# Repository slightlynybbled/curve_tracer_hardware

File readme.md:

# Purpose #

The purpose of this repository is to document the curve tracer project.  A
full description may be found at [for(embed)](http://www.forembed.com/project-curve-tracer-requirements.html).

# Project Repositories #

Be sure to check out the [firmware](https://github.com/slightlynybbled/curve_tracer_firmware) and 
[gui](https://github.com/slightlynybbled/curve_tracer_gui) repositories!

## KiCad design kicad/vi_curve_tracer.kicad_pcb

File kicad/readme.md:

# Electronics #

This directory contains the schematics and PCB layout (KiCad)

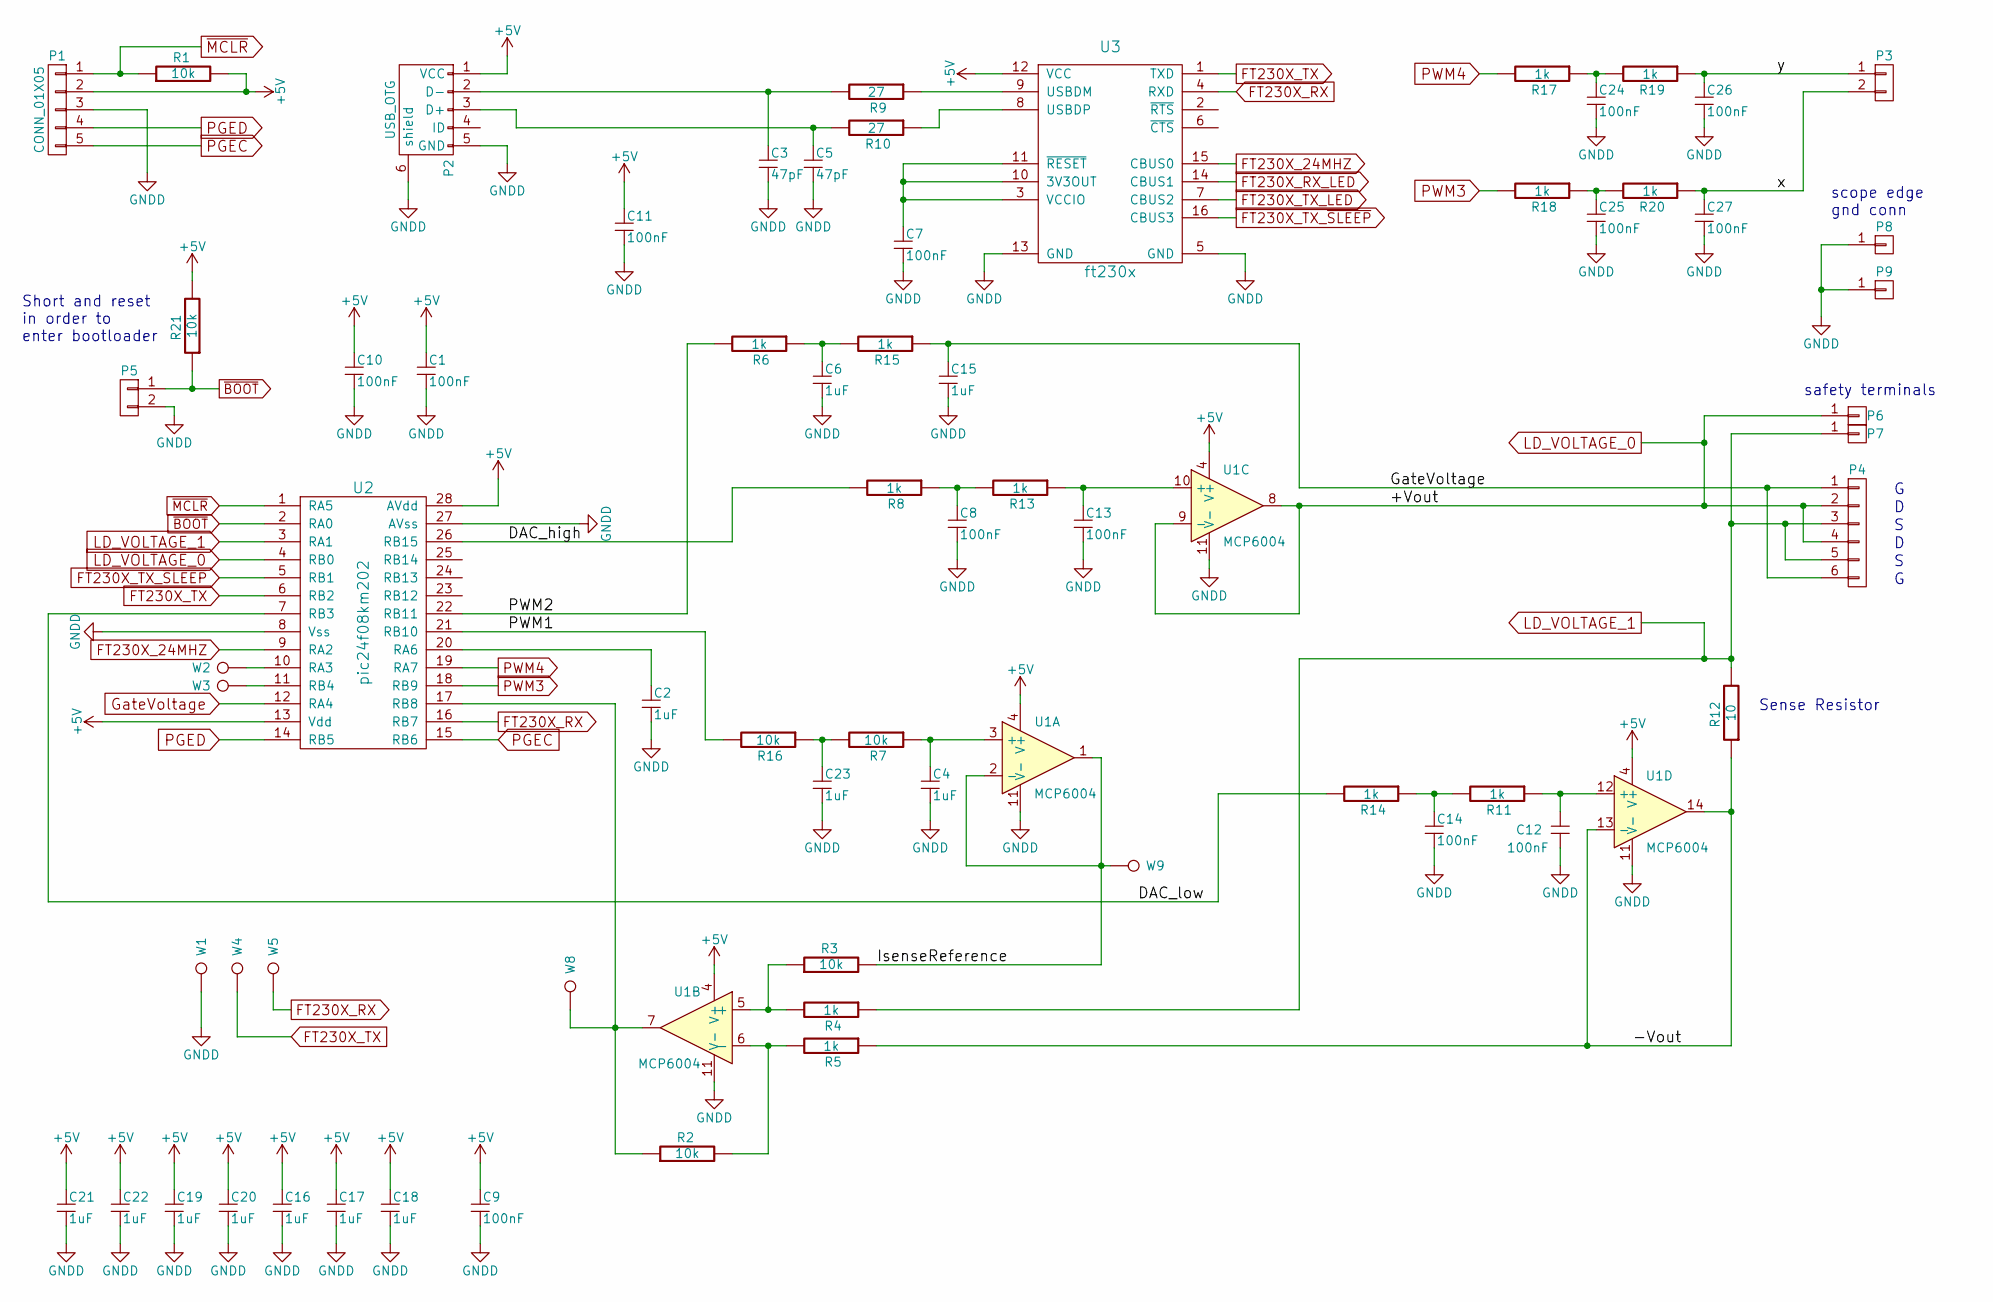
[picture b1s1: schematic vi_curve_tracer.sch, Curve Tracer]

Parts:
C1, C7, C8, C9, C10, C11, C12, C13, C14, C24, C25, C26, C27: 100nF; SM_0603; MPN CC0603ZRY5V7BB104
C2, C4, C6, C15, C16, C17, C18, C19, C20, C21, C22, C23: 1uF; SM_0603; MPN CC0603ZRY5V7BB105
C3, C5: 47pF; SM_0603; MPN C0603C470J3GACTU
P1: CONN_01X05; CONN_1x5_0.1in
P2: USB_OTG; CONN_USB; MPN DX4R005JJ2R1800
P3: CONN_01X02; CON_1x2_0.1in; MPN 0022284020
P4: CONN_01X06; CONN_2x3_SOCKET; MPN A06-LC-TT
P5: CONN_01X02; Pin_Header_Straight_1x02
P6: CONN_01X01; CONN_1x1_CT3150; MPN CT3150-2
P7: CONN_01X01; CONN_1x1_CT3150; MPN CT3150-0
P8, P9: CONN_01X01; CONN_1x1_EDGE_SCOPE_GND
R1, R2, R3, R7, R16, R21: 10k; SM_0603; MPN RC0603FR-0710KL
R4, R5, R6, R8, R11, R13, R14, R15, R17, R18, R19, R20: 1k; SM_0603; MPN RC0603FR-071KL
R9, R10: 27; SM_0603; MPN RC0603FR-0727RL
R12: 10; SM_0603; MPN RC0603FR-0710RL
U1: MCP6004; SSOP-14; MPN MCP6L04T-E/ST
U2: pic24f08km202; SSOP-28; MPN PIC24FV16KM202-I/SS
U3: ft230x; SOIC-16; MPN FT230XS-R
W1, W2, W3, W4, W5, W8, W9: TEST_1P; Measurement_Point_Round-SMD-Pad_Small

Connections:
+5V: C1.1, C9.1, C10.1, C11.1, C16.1, C17.1, C18.1, C19.1, C20.1, C21.1, C22.1, P1.2, P2.1 (VCC), R1.2, R21.2, U1.4 (V+), U2.13 (Vdd), U2.28 (AVdd), U3.12 (VCC)
/-Vout: R5.1, R12.1, U1.13 (-), U1.14
/DAC_high: R8.2, U2.26 (RB15)
/DAC_low: R14.2, U2.7 (RB3)
/IsenseReference: R3.2, U1.1, U1.2 (-), W9.1
/PWM1: R16.2, U2.21 (RB10)
/PWM2: R6.2, U2.22 (RB11)
/x: C27.1, P3.2, R20.1
/y: C26.1, P3.1, R19.1
FT230X_24MHZ: U2.9 (RA2), U3.15 (CBUS0)
FT230X_RX: U2.16 (RB7), U3.4 (RXD), W5.1
FT230X_TX: U2.6 (RB2), U3.1 (TXD), W4.1
FT230X_TX_~SLEEP: U2.5 (RB1), U3.16 (CBUS3)
GNDD: C1.2, C2.2, C3.2, C4.2, C5.2, C6.2, C7.2, C8.2, C9.2, C10.2, C11.2, C12.2, C13.2, C14.2, C15.2, C16.2, C17.2, C18.2, C19.2, C20.2, C21.2, C22.2, C23.2, C24.2, C25.2, C26.2, C27.2, P1.3, P2.5 (GND), P2.6 (shield), P5.2, P8.1, P9.1, U1.11 (V-), U2.8 (Vss), U2.27 (AVss), U3.5 (GND), U3.13 (GND), W1.1
GateVoltage: C15.1, P4.1, P4.6, R15.1, U2.12 (RA4)
LD_VOLTAGE_0: P4.2, P4.4, P6.1, U1.8, U1.9 (-), U2.4 (RB0)
LD_VOLTAGE_1: P4.3, P4.5, P7.1, R4.1, R12.2, U2.3 (RA1)
unnamed: C2.1, U2.20 (RA6)
unnamed: C3.1, P2.2 (D-), R9.2
unnamed: C4.1, R7.1, U1.3 (+)
unnamed: C5.1, P2.3 (D+), R10.2
unnamed: C6.1, R6.1, R15.2
unnamed: C7.1, U3.3 (VCCIO), U3.10 (3V3OUT), U3.11 (~RESET)
unnamed: C8.1, R8.1, R13.2
unnamed: C12.1, R11.1, U1.12 (+)
unnamed: C13.1, R13.1, U1.10 (+)
unnamed: C14.1, R11.2, R14.1
unnamed: C23.1, R7.2, R16.1
unnamed: C24.1, R17.1, R19.2
unnamed: C25.1, R18.1, R20.2
unnamed: R2.1, U1.7, U2.17 (RB8), W8.1
unnamed: R2.2, R5.2, U1.6 (-)
unnamed: R3.1, R4.2, U1.5 (+)
unnamed: R9.1, U3.9 (USBDM)
unnamed: R10.1, U3.8 (USBDP)
unnamed: U2.10 (RA3), W2.1
unnamed: U2.11 (RB4), W3.1
PGEC: P1.5, U2.15 (RB6)
PGED: P1.4, U2.14 (RB5)
PWM3: R18.2, U2.18 (RB9)
PWM4: R17.2, U2.19 (RA7)
~BOOT: P5.1, R21.1, U2.2 (RA0)
~MCLR: P1.1, R1.1, U2.1 (RA5)

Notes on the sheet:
Sense Resistor
Short and reset in order to enter bootloader
safety terminals
scope edge gnd conn

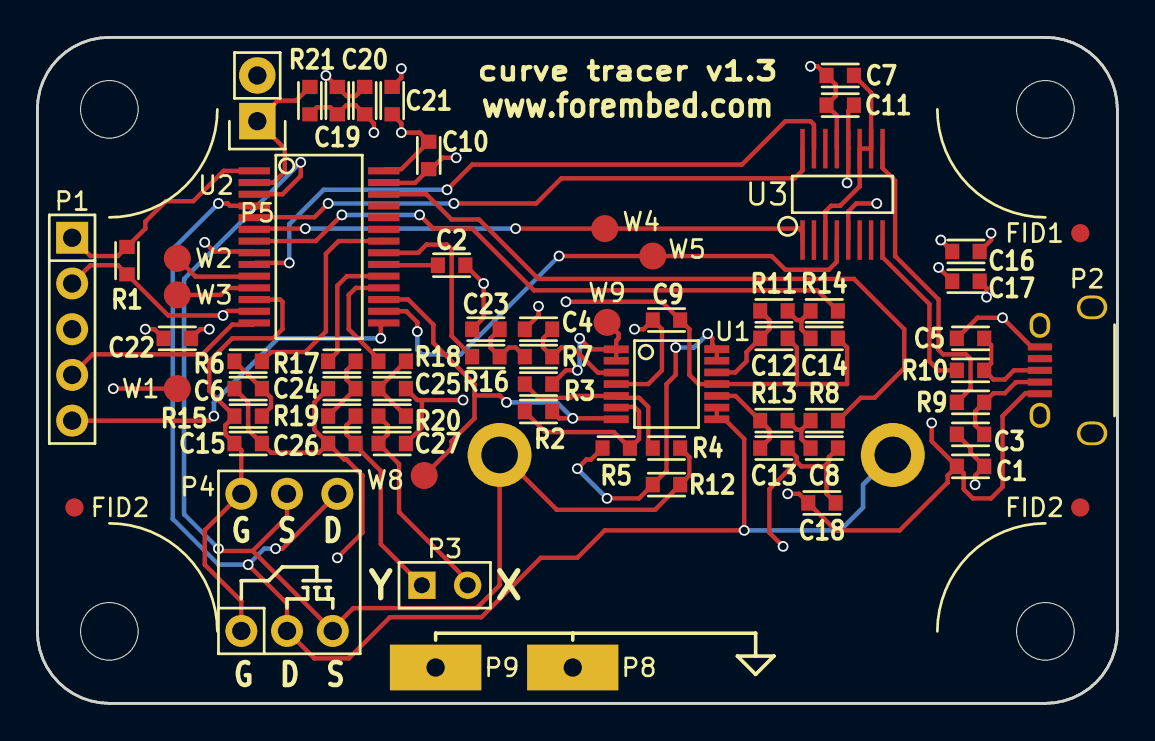
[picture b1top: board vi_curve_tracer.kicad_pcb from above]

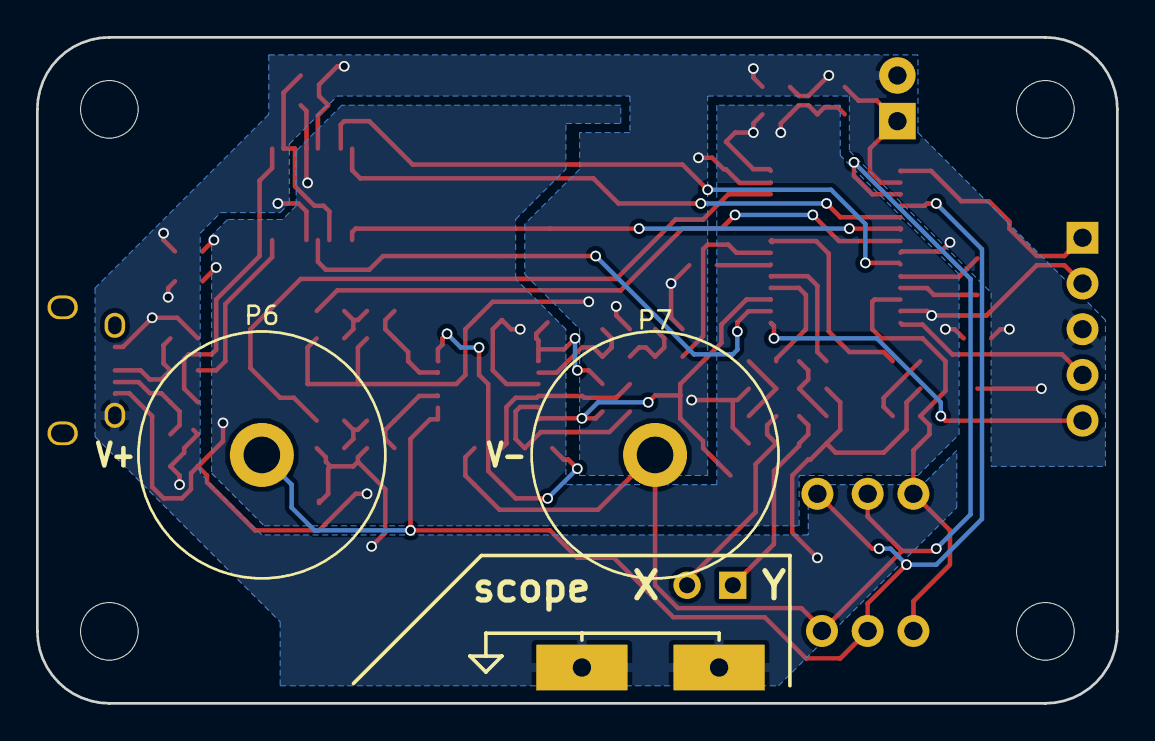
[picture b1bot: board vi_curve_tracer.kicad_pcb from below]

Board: 2 copper layers, 60.0 x 37.0 mm, 71 parts (2 on the bottom side), 43 nets.

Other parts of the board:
FID1, FID2, FID2#2: fiducial
SOB: case_sickOfBeige_60x37

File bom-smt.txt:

Item	Qty	Reference	Manufacturer	MPN	Description	Datasheet	
1	13	 C1, C7, C8, C9, C10, C11, C12, C13, C14, C24, C25, C26, C27	Yageo	CC0603ZRY5V7BB104	capacitor, 100nF, 0603		
2	12	 C2, C4, C6, C15, C16, C17, C18, C19, C20, C21, C22, C23	Yageo	CC0603ZRY5V7BB105	capacitor, 1uF, 0603		
3	2	 C3, C5	Kemet	C0603C470J3GACTU	capacitor, 47pF, 0603		
5	1	 P2	JAE Electronics	DX4R005JJ2R1800	Conn USB Micro-B		
6	1	 P3	Molex	0022284020	header, 0.1in, 2-pos		
7	1	 P4	Assmann WSW Components	A06-LC-TT	DIP socket, 2x3		
10	6	 R1, R2, R3, R7, R16, R21	Yageo	RC0603FR-0710KL	resistor, 10kohm, 0603		
11	1	 R12	Yageo	RC0603FR-0710RL	resistor, 10ohm, 0603		
12	12	 R4, R5, R6, R8, R11, R13, R14, R15, R17, R18, R19, R20	Yageo	RC0603FR-071KL	resistor, 1kohm, 0603		
13	2	 R9, R10	Yageo	RC0603FR-0727RL	resistor, 27ohm, 0603		
14	1	 U1	Microchip	MCP6L04T-E/ST	Opamp 1MHz, Quad, TSSOP-14		
15	1	 U2	Microchip, Inc.	PIC24FV16KM202-I/SS	Microcontroller		
16	1	 U3	FTDI	FT230XS-R	USB-to-UART, IC, SSOP-16

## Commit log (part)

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2016-02-12 Adding all electronic files relating to the curve tracer project.
2016-02-13 Made a quick start on the code. Compiles and simulates
2016-02-14 Added sine wave generation to the timer interrupt, reduced timer interrupt frequency
2016-02-18 Moved 'theta' into a static local variable'
2016-02-23 DAC is working
2016-02-23 DAC working @ double the frequency
2016-02-23 Added readme for code
2016-02-23 Modified link in readme
2016-02-24 Opamp appears to be working as a comparator, need to investigate the register settings
2016-02-24 Fixed opamp register, opamp now reflects DAC output
2016-02-24 Modified opamp setup for lower-bandwidth operation since high bandwidth is not required for the application
2016-02-25 Have PWM output working, frequency appears off by a factor of 2
2016-02-26 PWM module working well
2016-02-26 Modified PWM period register to 1024
2016-02-26 Changed the order of PWM initialization
2016-02-26 Split 'setDutyCycle' into 'setDutyCycleHZ1' and 'setDutyCycleHZ2
2016-03-01 Have A/D nominally working, need to test and verify functionality
2016-03-01 Added some defines to make code easier to read
2016-03-01 Have ADC working as a multiplexed input, not functioning correctly yet
2016-03-02 Modified multiplexing and speed of T1 interrupt
2016-03-02 Now making low-frequency measurements of hi-Z outputs while maintaining high-frequency measurements of the other three voltages
2016-03-02 All ADC interrupts occur within one T1 interrupt
2016-03-02 Some cleanup, increased size of data arrays
2016-03-02 Made the schematic more closely resemble the rework performed.
2016-03-02 Added a proper markdown link
2016-03-02 Saved schematic w/ program closed
2016-03-02 Added some test data
2016-03-03 Copied task manager source files
2016-03-03 Task manager initialized and ready
2016-03-04 Corrected CCT3 interrupt from CCP3 interrupt
2016-03-04 Updated system tick to 1ms @ 16MIPS, added two tasks
2016-03-10 Reduced data buffer size
2016-03-10 Removed unnecessary tasks
2016-03-11 Basic UART functioning
2016-03-20 Moved DIO and UART libraries to their own files
2016-03-22 Changed system tick from the 16MHz frequency to the 12MHz frequency
2016-03-22 Implemented and debugged UART functions
2016-03-22 Removed some space in file
2016-03-22 Moved the uart code to the telemetry lib. Modified main so that telemetry works as a transmitter
2016-03-23 Re-added UART interface - removing references to telemetry lib
2016-03-23 Modified UART functions to reduce overhead
2016-03-23 Modified with latest version of the cbuffer lib
2016-03-23 Modified UART lib to be compatible with the new circular buffer format
2016-03-23 Short loop-back test that ensures that the buffers are working properly
2016-03-24 Added framing code
2016-03-24 Modified main.c to use framing instead of the UART directly
2016-03-24 Have framing completed along with a short verification script in python
2016-03-29 Added frame code
2016-04-05 Telemetry-like serial protocol is working on pubserial
2016-04-05 Fixed several bugs involving the translation of 16-bit to 8-bit
2016-04-05 Fixed an error involving multi-dimensional data of > 2 dimensions
2016-04-05 Added proper string processing
2016-04-05 Refactored some variables
2016-04-05 Adding subscription infrastructure, reduced buffer sizes to reduce RAM usage
2016-04-05 Adding Python framework classes to easily handle the data coming into the serial port on the PC side
2016-04-05 Debugged callbacks in python class
2016-04-06 Finished subscriber on pubser
2016-04-06 Fixed a while loop error
2016-04-07 Fixed some errors in subscription, completed implementation of subscription and data retrieval code
2016-04-07 Compacted one statement
2016-04-07 Refactored some code, added docstrings to PUB
2016-04-07 Added a subscriber for testing
2016-04-07 Added docstrings to frame
2016-04-07 Moved some buffer lengths to the header file
2016-04-07 Move frame defines to the header file
2016-04-07 Moved defines to header file, refactored one define
2016-04-08 Moved the config out of main.c
2016-04-08 Added docstrings to classes and class methods
2016-04-08 Added library callout to the readme
2016-04-10 Added ability to plot using tkinter
2016-04-10 Basic plotting is working, but needs to re-draw the plot periodically in order to remove old data
2016-04-10 Fixed an error in sign, have small amount of data being passed for testing purposes
2016-04-10 Successfully erasing points
2016-04-10 Added ability for frame to write incrementally to the UART buffer
2016-04-10 Increased RAM efficiency of writes to UART
2016-04-10 Removed unnecessary define
2016-04-10 Sending 64 datapoints back to PC every 0.5s
2016-04-10 Increased pubserial buffer size
2016-04-10 Increased buffer size and fied some potential glitches
2016-04-10 Plotting 64 points now
2016-04-11 Added ability to change omega setting using a subscriber
2016-04-25 Pulling serial lib from Dispatch and using PyDispatch for the visualization
2016-04-29 Added Dispatch drivers to this code for configuration purposes
2016-04-29 Revised Dispatch configuration file for most recent Dispatch version
2016-04-29 Plotting voltage to find potential issues
2016-04-29 Sampling occuring at evenly-spaced intervals now
2016-04-29 Works, appears to be working well on the screen captures
2016-05-03 Added electronics files, nearly complete
2016-05-03 DIS_init() should occur after the channel assignments
2016-05-05 Updated electronics with most recent layout and schematic
2016-05-17 Added write enable for when dispatch is transmitting
2016-05-18 Added error messages at compile time when the UART buffers are inappropriately sized.
2016-05-19 Moving driver improvements from Dispatch
2016-05-19 Increased frequency of sending data
2016-05-23 Removed old test files, changed 'code' directory to 'c' directory
2016-05-23 Adding python files for the desktop application
2016-05-23 Changed from the local 'PyDispatch' to the distributed 'SerialDispatch' from PiPI
2016-05-23 Changed part to the industrial temp range
2016-05-23 Made frequency status update based on the received 'frequency' message
2016-05-24 Added readme to python application directory
2016-05-24 Added ability to change the frequency using the <Return> key
2016-05-24 Added frequency setting window to 'Edit'
2016-05-25 Added frequency conversion to C code and modified app.py appropriately to send to 'frequency' instead of 'omega'
2016-05-25 Update readme link
2016-05-25 Added .gitignore file
2016-05-26 Removed unnecessary electronics files
2016-05-27 #4 Port code works, but it appears that the waveform is distorted. Perhaps the DAC needs a higher impedance on it than 1k?
2016-05-27 #4 Port complete for C code, had to move DAC outputs to opamp outputs on board to improve impedance
2016-05-27 Added comments, organized code into sections, no functional change
2016-05-27 Re-worked frequency-setting scheme to a much higher precision model
2016-05-27 Analog section now working quite well, removed unnecessary code
2016-05-27 Added labels to each axis
2016-05-27 Added a small attenuation factor for the output sine wave in order to avoid saturating the opamp output. This mildly limits the range of the output voltage, but vastly decreases harmonics.
2016-05-27 Changed filter resistors to 3.3k
2016-05-27 Corrected y-axis label
2016-05-27 Moved x-axis label left by 5px
2016-05-30 Corrected DAC sample rate to ADC sample rate
2016-05-30 Changed vertical scaling from 500uA/div to 5mA/div by reducing opamp gain and by changing the label in the GUI
2016-05-30 Changed R7 to increase filter effectiveness
2016-05-30 Removed attenuation factor - as hardware filtering became more accurate, the attenuation became unnecessary
2016-05-30 Increased the output filter frequency cutoff
2016-05-31 Changed the newPeriod to 2000 since the shortest period should be 1000
2016-06-02 Minor rev of electronics, added BOM
2016-06-02 Modified calls to Dispatch to use the lower-memory versions
2016-06-02 Modified spacing to make defines easier to read
2016-06-02 See #6 - Added functions to send and receive the calibration directive from the Python script
2016-06-02 Fixes #6 - Offset calibration complete and working
2016-06-02 See #5 - Added manual setting of gate voltage
2016-06-02 See #5 - Added status bar indicator for the gate voltage
2016-06-02 See #5 - Added output mode selector image
2016-06-03 See #5 - Can software-control the gate using the GUI
2016-06-03 See #5 - Added patch wire to control the gate voltage
2016-06-03 See #5 - Mild refactor, no functional change
2016-06-03 See #5 - Implemented a three-terminal mode, still needs some work
2016-06-06 Fixes #5 - 3-terminal mode added, works well
2016-06-06 Sent data is now 16-bit instead of 8-bit
2016-06-06 Removed unnecessary writelock
2016-06-06 Changed initial frequency to 60Hz
2016-06-06 Removed debugging port change
2016-06-06 Transitioned to points instead of lines
2016-06-06 Doubled the number of points being sent
2016-06-06 Increased samples to be buffered
2016-06-06 Fixed frequency-setting problem
2016-06-06 Fixes #8 - Added ground reference on the terminal block
2016-06-07 Fixes #9 - Can adjust the amplitude of the waveform
2016-06-07 Minor optimization in complimentary sine wave generation
2016-06-07 Fixes #11 - waveform frequency, amplitude, and offset are moved into their own dialog box
2016-06-09 See #13 - Added code that will output XY mode to any oscilloscope
2016-06-09 Increased update rate for data
2016-06-09 Updates to GUI and frequencies
2016-06-09 Added scatter ploting to 'plot4q' in order to make the drawing of data more smooth
2016-06-09 Changed 'message' to 'label' tkinter types
2016-06-09 Closes #2, adds a read button that is not fully implemented yet (see #3)
2016-06-10 Added erase image, removed white bg from load btn
2016-06-10 Fixed #3 - Added ability to load waveforms to screen, but only one at a time
2016-06-10 Appear to have solved a race condition that caused random points to be erased or written to the canvas due to multiple threads competing for that canvas. Needs more testing and scatter method needs t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
2016-06-10 Small refactor to increase efficiency of scatter() method, no change in function
2016-06-11 Converted to using images instead of ovals on the canvas
2016-06-11 Added extra header to short in case we want to add a bootloader later
2016-06-11 Slight modification to open and save menus
2016-06-12 Using ovals to draw the points
2016-06-13 Ensured that the index is only reset when the ramp is going in one direction to make plots more consistent.
2016-06-13 Moving points instead of creating them on the plot
2016-06-13 Removed redundant variable
2016-06-14 Removed unnecessary print
2016-06-14 See #16 - Added buttons, but not functionality yet
2016-06-14 Removed unnecessary parameter
2016-06-14 See #16 - added basic images for the pause and play buttons
2016-06-14 Fixes #16 - Pause and run works
2016-06-14 Updated BOM items based on feedback from octopart, added fiducials to layout
2016-06-14 Added gerber
2016-06-14 Cleaned up image directory of unused images
2016-06-14 Removed unnecessary files
2016-06-14 Moved kicad files from 'electronics' to 'kicad' directory
2016-06-14 Moved schematic out of kicad directory
2016-06-14 Moved 'bom.txt' outside of kicad directory
2016-06-14 Moved gerber files outside of the kicad directory
2016-06-14 Included links to firmware and gui repositories
2016-06-14 Changed heading
2016-06-20 Added safety (multimeter) probes for maximimum compatiblity with likely components that the user already has
2016-06-20 Added some CAD models to make visualization of case easier
2016-06-22 Modeling in solidworks, designing the case
2016-07-08 Added features to allow connecting to oscilloscope easier, no change to function.
2016-07-08 Added new gerber files for v1.2
2016-07-08 PDF copy of schematic
2016-07-08 Added BOM information
2016-07-08 Moved points to make case design a bit easier
2016-07-08 Modified case design to make it easier to cut
2016-07-13 Added MIT license
2016-08-13 Fixed BOM issue
2017-06-07 Removed gerber files
2017-06-07 Updated to v1.3
2017-07-20 Update link
2017-09-14 Added fiducial
